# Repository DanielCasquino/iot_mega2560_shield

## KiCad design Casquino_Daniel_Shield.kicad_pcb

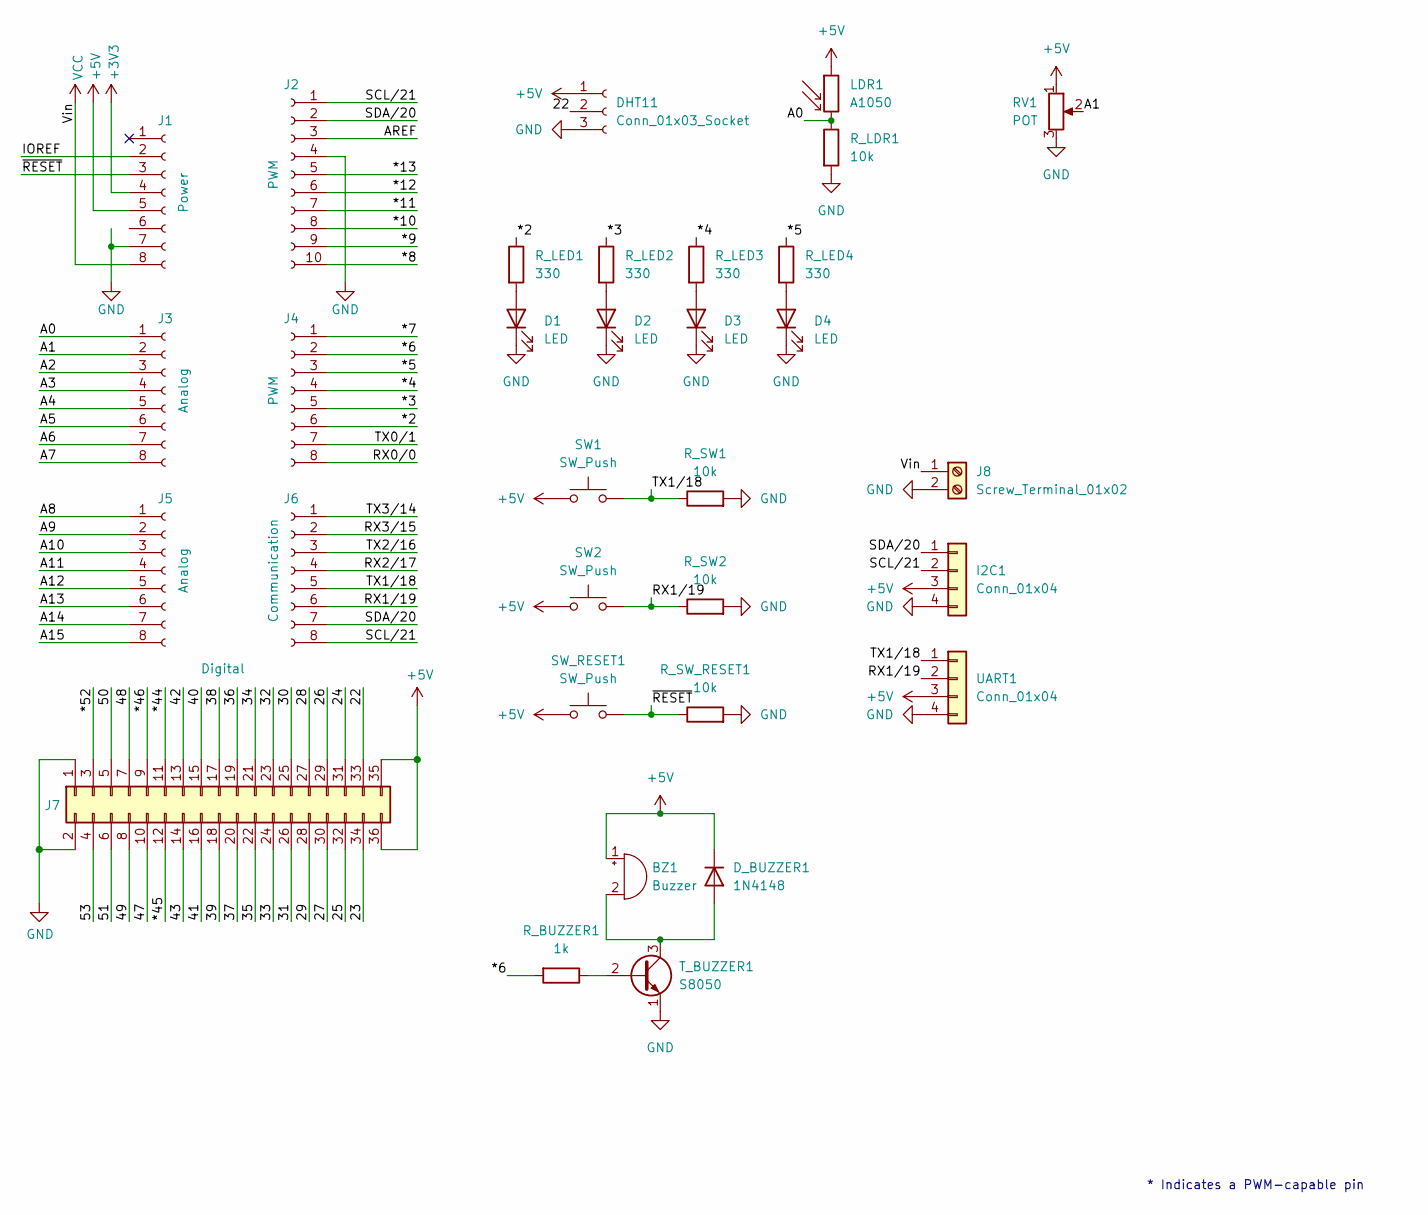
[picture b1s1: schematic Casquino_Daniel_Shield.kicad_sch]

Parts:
BZ1: Buzzer; Buzzer_12x9.5RM7.6
D1, D2, D3, D4: LED; LED_D5.0mm
DHT11: Conn_01x03_Socket; PinSocket_1x03_P2.54mm_Vertical
D_BUZZER1: 1N4148; D_DO-35_SOD27_P7.62mm_Horizontal
I2C1: Conn_01x04; Molex_KK-254_AE-6410-04A_1x04_P2.54mm_Vertical
J1: Power; PinSocket_1x08_P2.54mm_Vertical
J2: PWM; PinSocket_1x10_P2.54mm_Vertical
J3, J5: Analog; PinSocket_1x08_P2.54mm_Vertical
J4: PWM; PinSocket_1x08_P2.54mm_Vertical
J6: Communication; PinSocket_1x08_P2.54mm_Vertical
J7: Digital; PinSocket_2x18_P2.54mm_Vertical
J8: Screw_Terminal_01x02; TerminalBlock_Phoenix_MKDS-1,5-2-5.08_1x02_P5.08mm_Horizont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
LDR1: A1050; R_LDR_D6.4mm_P3.4mm_Vertical
RV1: POT; Potentiometer_Bourns_3386P_Vertical
R_BUZZER1: 1k; R_Axial_DIN0207_L6.3mm_D2.5mm_P7.62mm_Horizontal
R_LDR1: 10k; R_Axial_DIN0207_L6.3mm_D2.5mm_P7.62mm_Horizontal
R_LED1, R_LED2, R_LED3, R_LED4: 330; R_Axial_DIN0207_L6.3mm_D2.5mm_P7.62mm_Horizontal
R_SW1, R_SW2: 10k; R_Axial_DIN0207_L6.3mm_D2.5mm_P7.62mm_Horizontal
R_SW_RESET1: 10k; R_Axial_DIN0207_L6.3mm_D2.5mm_P7.62mm_Horizontal
SW1, SW2: SW_Push; SW_PUSH_6mm
SW_RESET1: SW_Push; SW_PUSH_6mm
T_BUZZER1: S8050; TO-92_Inline
UART1: Conn_01x04; Molex_KK-254_AE-6410-04A_1x04_P2.54mm_Vertical

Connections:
+3V3: J1.4
+5V: BZ1.1 (+), DHT11.1, D_BUZZER1.1 (K), I2C1.3, J1.5, J7.35, J7.36, LDR1.1, RV1.1, SW1.1, SW2.1, SW_RESET1.1, UART1.3
/22: DHT11.2, J7.33
/23: J7.34
/24: J7.31
/25: J7.32
/26: J7.29
/27: J7.30
/28: J7.27
/29: J7.28
/30: J7.25
/31: J7.26
/32: J7.23
/33: J7.24
/34: J7.21
/35: J7.22
/36: J7.19
/37: J7.20
/38: J7.17
/39: J7.18
/40: J7.15
/41: J7.16
/42: J7.13
/43: J7.14
/47: J7.10
/48: J7.7
/49: J7.8
/50: J7.5
/51: J7.6
/53: J7.4
/*2: J4.6, R_LED1.1
/*3: J4.5, R_LED2.1
/*4: J4.4, R_LED3.1
/*5: J4.3, R_LED4.1
/*6: J4.2, R_BUZZER1.2
/*7: J4.1
/*8: J2.10
/*9: J2.9
/*10: J2.8
/*11: J2.7
/*12: J2.6
/*13: J2.5
/*44: J7.11
/*45: J7.12
/*46: J7.9
/*52: J7.3
/A0: J3.1, LDR1.2, R_LDR1.1
/A1: J3.2, RV1.2
/A2: J3.3
/A3: J3.4
/A4: J3.5
/A5: J3.6
/A6: J3.7
/A7: J3.8
/A8: J5.1
/A9: J5.2
/A10: J5.3
/A11: J5.4
/A12: J5.5
/A13: J5.6
/A14: J5.7
/A15: J5.8
/AREF: J2.3
/IOREF: J1.2
/RX0/0: J4.8
/RX1/19: J6.6, R_SW2.1, SW2.2, UART1.2
/RX2/17: J6.4
/RX3/15: J6.2
/SCL/21: I2C1.2, J2.1, J6.8
/SDA/20: I2C1.1, J2.2, J6.7
/TX0/1: J4.7
/TX1/18: J6.5, R_SW1.1, SW1.2, UART1.1
/TX2/16: J6.3
/TX3/14: J6.1
/~RESET: J1.3, R_SW_RESET1.1, SW_RESET1.2
GND: D1.1 (K), D2.1 (K), D3.1 (K), D4.1 (K), DHT11.3, I2C1.4, J1.7, J2.4, J7.1, J7.2, J8.2, RV1.3, R_LDR1.2, R_SW1.2, R_SW2.2, R_SW_RESET1.2, T_BUZZER1.1 (E), UART1.4
unnamed: BZ1.2 (-), D_BUZZER1.2 (A), T_BUZZER1.3 (C)
unnamed: D1.2 (A), R_LED1.2
unnamed: D2.2 (A), R_LED2.2
unnamed: D3.2 (A), R_LED3.2
unnamed: D4.2 (A), R_LED4.2
unnamed: R_BUZZER1.1, T_BUZZER1.2 (B)
VCC: J1.8, J8.1

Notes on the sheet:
* Indicates a PWM-capable pin

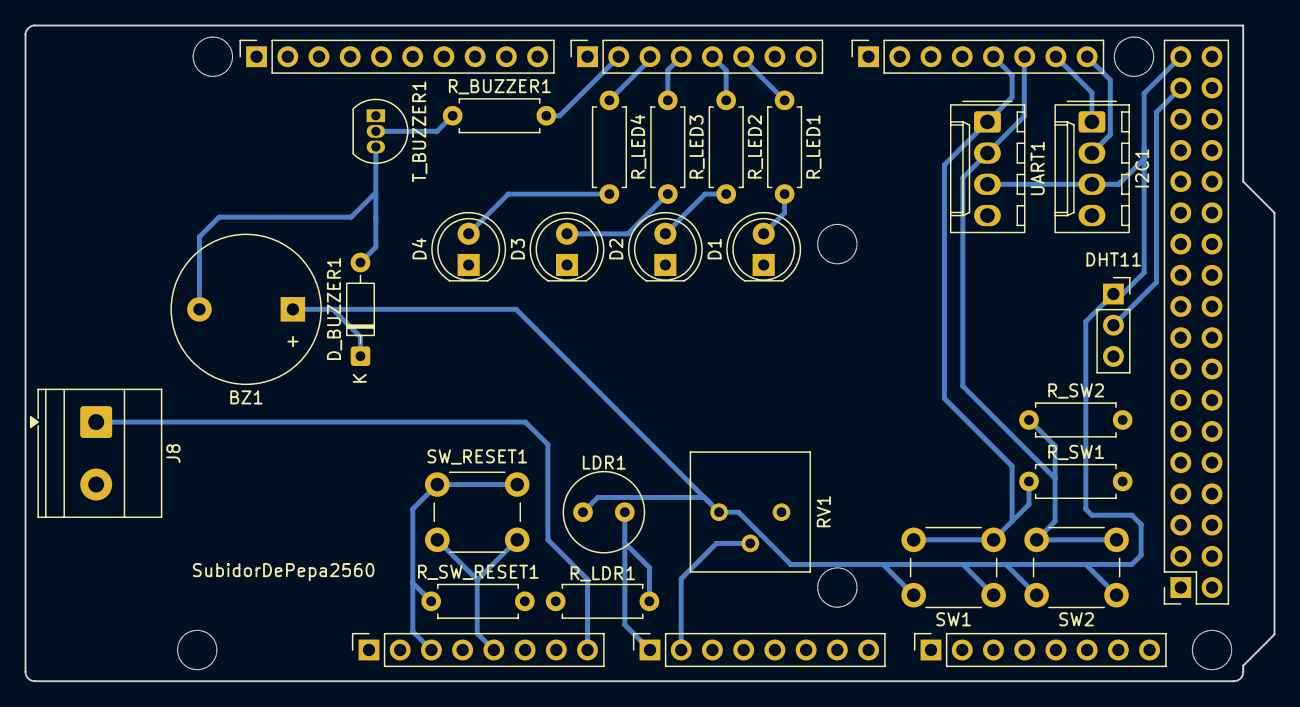
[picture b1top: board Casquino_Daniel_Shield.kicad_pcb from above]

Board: 2 copper layers, 101.6 x 53.3 mm, 38 parts (0 on the bottom side), 22 nets.

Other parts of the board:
MH1, MH2, MH3, MH4, MH5, MH6: MountingHole_3.2mm
